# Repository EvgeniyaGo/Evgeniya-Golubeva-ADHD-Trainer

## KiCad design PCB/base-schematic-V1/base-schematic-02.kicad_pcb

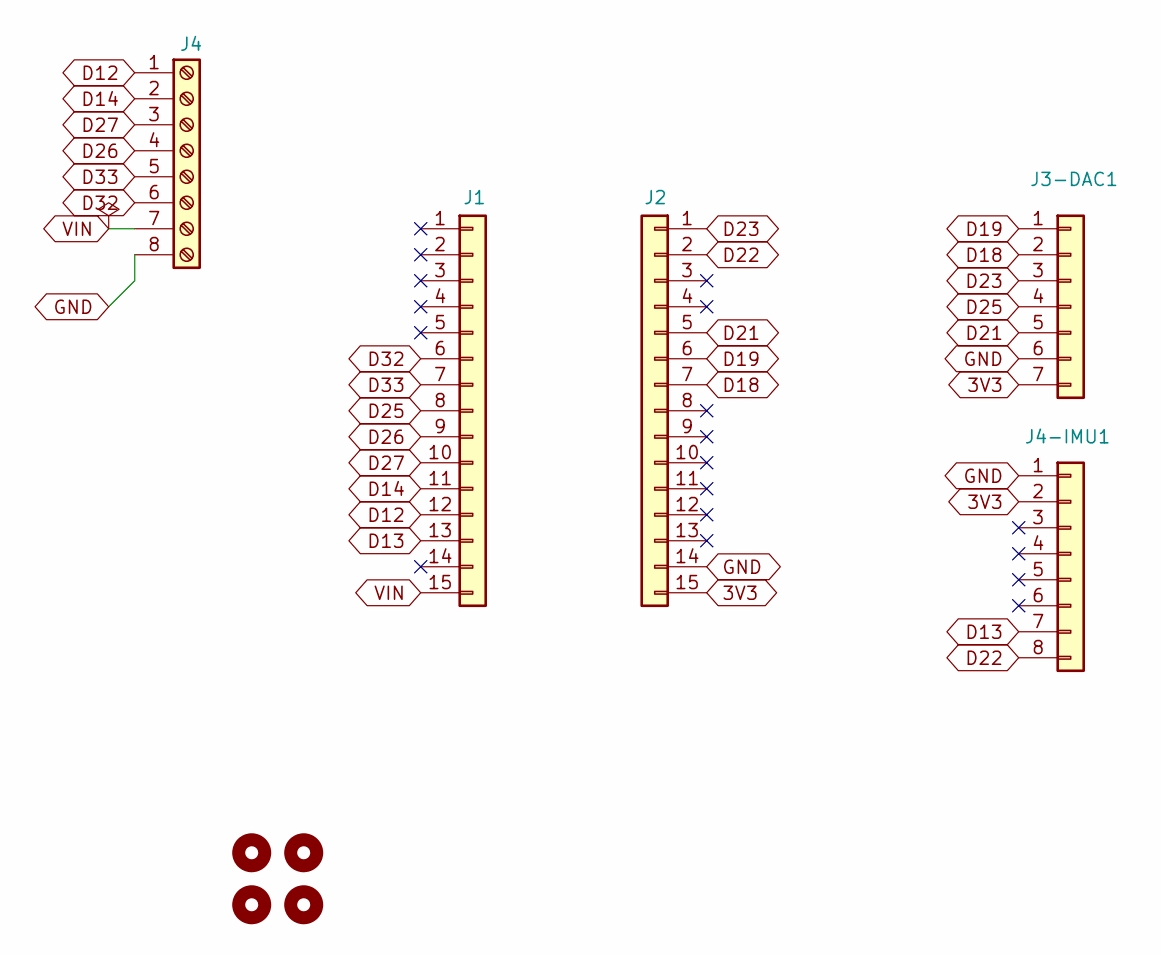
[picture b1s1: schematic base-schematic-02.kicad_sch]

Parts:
H1, H2, H3, H4: MountingHole; MountingHole_3.2mm_M3
J1, J2: Conn_01x15; PinSocket_1x15_P2.54mm_Vertical
J3-DAC1: Conn_01x07; PinSocket_1x07_P2.54mm_Vertical
J4: Screw_Terminal_01x08; TerminalBlock_Phoenix_PT-1,5-8-3.5-H_1x08_P3.50mm_Horizontal
J4-IMU1: Conn_01x08; PinSocket_1x08_P2.54mm_Vertical

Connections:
3V3: J2.15, J3-DAC1.7, J4-IMU1.2
D12: J1.12, J4.1
D13: J1.13, J4-IMU1.7
D14: J1.11, J4.2
D18: J2.7, J3-DAC1.2
D19: J2.6, J3-DAC1.1
D21: J2.5, J3-DAC1.5
D22: J2.2, J4-IMU1.8
D23: J2.1, J3-DAC1.3
D25: J1.8, J3-DAC1.4
D26: J1.9, J4.4
D27: J1.10, J4.3
D32: J1.6, J4.6
D33: J1.7, J4.5
GND: J2.14, J3-DAC1.6, J4.8, J4-IMU1.1
VIN: J1.15, J4.7

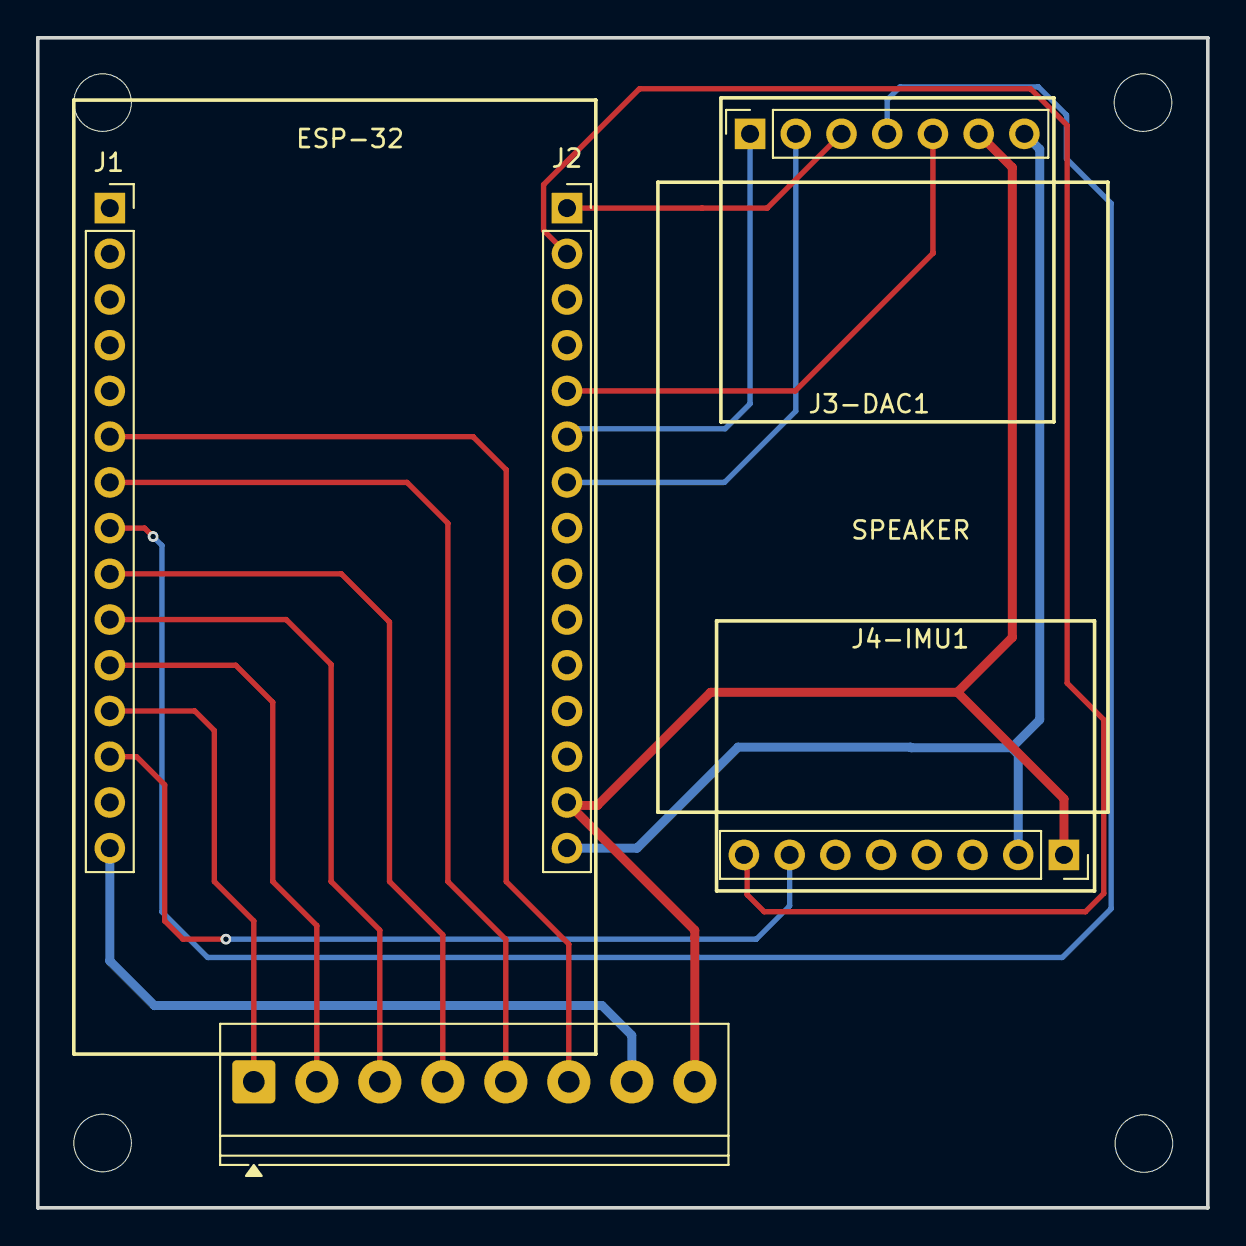
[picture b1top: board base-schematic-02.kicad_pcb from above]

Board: 2 copper layers, 65.0 x 65.0 mm, 9 parts (0 on the bottom side), 16 nets.

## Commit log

2025-10-11 ESP32 first connection success
    first TX/RX connection with phone via nRF. Did not see the name of the board, but figured out which is it by the rate of ~20ms, which is low enough for the distance.
    Next - make sure the board ahs a proper name and go to making the app.
2025-10-13 Connects to react without a problem
    Now with the code rewritten, it connects to the phone without problems. It also displays as Jeni-ESP32.
2025-10-13 Init the app and edited App.tsx to establish communication w/ ESP and showcase it via echo
    The result is something along the lines of:
    [BLE] Connected to Jeni-ESP32
    [→ ESP] "hello\n"
    [ESP →] hello
2025-10-15 Yet another setup commit
2025-10-27 Some better basic design for the app
    Added pages and made it look like at least partially real website.
2025-10-27 Which face is facing upwards algorithm
    Will be needed later for checking motion and submitting answers.
    - Almost none to none noise
    - Based on an MPU6050 (might change later but the code should remain almost the same)
    Recognizes which face is upwards and, when it has changed, writes a new print into serial.
    Next step is the shake recognition.
2025-11-01 Box with 6 leds (stage 1)
    Mimiccing the box movement detection
2025-11-01 Box lightning up via IMU movement
    Implement ADXL345-based face detection and LED orientation display
2025-11-02 Restart the app with new pages and approach
    I am changing the approach from building a lot of different small things and later connecting them to connecting them onto one stable from beginning structure. For this I changed the code for the app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
    Also fixed the nesting problems.
2025-11-02 Fixed all problems with includes in the app
    56 (?) problems fixed.
2025-11-02 Led control of the cube from App
    Now I have a boolean that works as an "app-permission". When the app sends a signal, this puts the boolean to the opposite value. The whole led control is put inside an if, depending on this value.
    Also, there is a communication esp -> app via sending to the app state of each side boolean (led_up and so on) each ~4 seconds.
2025-11-03 Two 10x10 panels
    Somehow a 8x8 and 10x10 have a lot of problems working together. However one 8x8 or two 10x10 have no problems. Next are shapes on the 10x10s
2025-11-03 Panel 10x10 draw thin and thick shapes
    This took longer than it should have... There are hardcoded shapes and a mask-like-recognizer of the shape code.
2025-11-03 Shapes circling working
2025-11-05 Final testing of 10x10 for measuring the current
    One fully white 10x10 on 128/255 brightness takes less than 400 mA.
2025-11-05 Init commit
    Make it work after it mystiriously broke again... I swear its possessed
2025-11-05 Connected Matrix to LED logic via IMU control
2025-11-05 Some app changes
2025-11-05 App main screen prototype for desktop and mobile beautification
2025-11-05 Combine imu and led code with matrix
2025-11-06 Working 2-display imu-to-display orientation game
    Each trial chooses a target face (random) and shows a small 2×2 square on that face.
    Headstart (2s): just a cue/preamble; no penalties. (We still display the small square.)
    Discovery window (5s): player must get the target face up at least once before t = 7s.
    Hold (3s continuous): once started, the face must remain up without breaking.
    Feedback (3s): Success → enlarge square to a bigger block (e.g., 4×4) in green for 3s. Fail → enlarge square to red for 3s.
    Loop to next trial.
2025-11-16 6 Sides of the cube are on
    - Making a v2 prototype with 6 sides lighting up
2025-11-17 Final code for lost packets connetion testing
2025-12-22 Small finishes by different topics
    - Speaker
    - IMU
    - Display controls
    - Diffusers
2026-01-03 PCB creations
2026-01-23 Cube positioning fixing (pointing one side to another)
2026-01-23 Move arrow logic to server code. Create a clear all. Fix overlays.
2026-01-24 Got start round to work, end round stilll in process
    START ROUND manually works
    At rounds end esp sends an END ROUND
    Server gets:
    [ESP →] END ROUND LEFT
    [ESP →] [45 4e 44 20 52 4f 55 4e 44 20 4c 45 46 54 0a]
    So a weird hex is there. And the server does not send another command to "run next round."
2026-01-24 End round command works. Endless automated loop
2026-01-26 Added audio signal (after resoldering a new dac)
2026-01-30 Balancing half works
2026-01-30 balance working (still not sending end round)
2026-01-30 Auto round start for n remaining with side consistency and working end round
    [→ ESP] "ROUND START type=ARROW from=TOP to=Right duration=800 remaining=5"
    [ESP →] OK ROUND START
    [ESP →] ROUND BALANCE side=RIGHT
    [→ ESP] "CLEAR ALL"
    [→ ESP] "DRAW SHAPE RIGHT SHAPE_ARROW_RIGHT COLOR_BLUE"
    [→ ESP] "DRAW SHAPE RIGHT SHAPE_CIRCLE_6X6 COLOR_GREEN"
2026-01-30 round errors now return success/fail and reason + time
2026-01-31 Visual countdown now works
2026-01-31 Fix countdown sequencing, add a PAUSE logic, and make all round invariants work
2026-02-03 Add opposite side (Dimon says) game mode logic + Fix the ESP not appearing when powered from battery
2026-02-03 Fix opposite side logic for Dimon says
2026-02-04 Make the gameflow smooth and no bugs during it
2026-02-04 Debuged game flow. Added game start and game end commands
2026-02-05 Rewriring for V3 PCB + Adaptive difficulty through time
2026-02-05 Fixíng the countdown on front flickering
    Slowly rebuilding the loop on the bottom
2026-02-05 Countdown on ble fixed (still have to rewrite the real loop)
2026-02-06 Fixing issues with signals to player (beep, arrow, expected face)
    1. Cannot recognize the BEEP command (BEEP freq=... dur=...) - gives error command
    2. When server sends "draw arrow" it doesnt draw it. It draws the circle however. Maybe its because the arrow is on the side that the countdown is on?
    3. I get result=success on face=front where we are expecting right It appears that the face that is considered success is the "from" not expected nor to. [6:39:22 PM] [→ ESP] "ROUND START type=ARROW 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
2026-02-07 Fixed the countdown, now it follows the upFace on type ARROW
2026-02-07 Fixing round balance being updated too much and sending face=Unknown
2026-02-07 Fixing flickering screen back->top movement and back mirroring top
2026-02-09 Fixed clearing on round start
2026-02-15 Code clearing and comments
2026-02-15 PCB folder cleanup
2026-02-17 Adding electrical schematic
2026-02-17 Rename electrical_scehamatic.png to electrical_schematic.png
2026-02-17 Cleanup of App part
2026-05-02 Snake head moving across all 6 sides
2026-05-02 Add length (tail) to the snake
2026-05-03 apple spawning and growth
2026-05-11 Fixes to snake game - audio, faces
2026-05-17 Frontend
2026-05-17 Backend
2026-05-17 Reconnect app and cube and add some reimplementation of the protocol
    This took too long I am going insane please send help why is my pending round structure so f-ed up...
2026-05-19 Connect full gameplay logic
    Made the app pages actually display and control the gameplay.
    Added stats for game results
